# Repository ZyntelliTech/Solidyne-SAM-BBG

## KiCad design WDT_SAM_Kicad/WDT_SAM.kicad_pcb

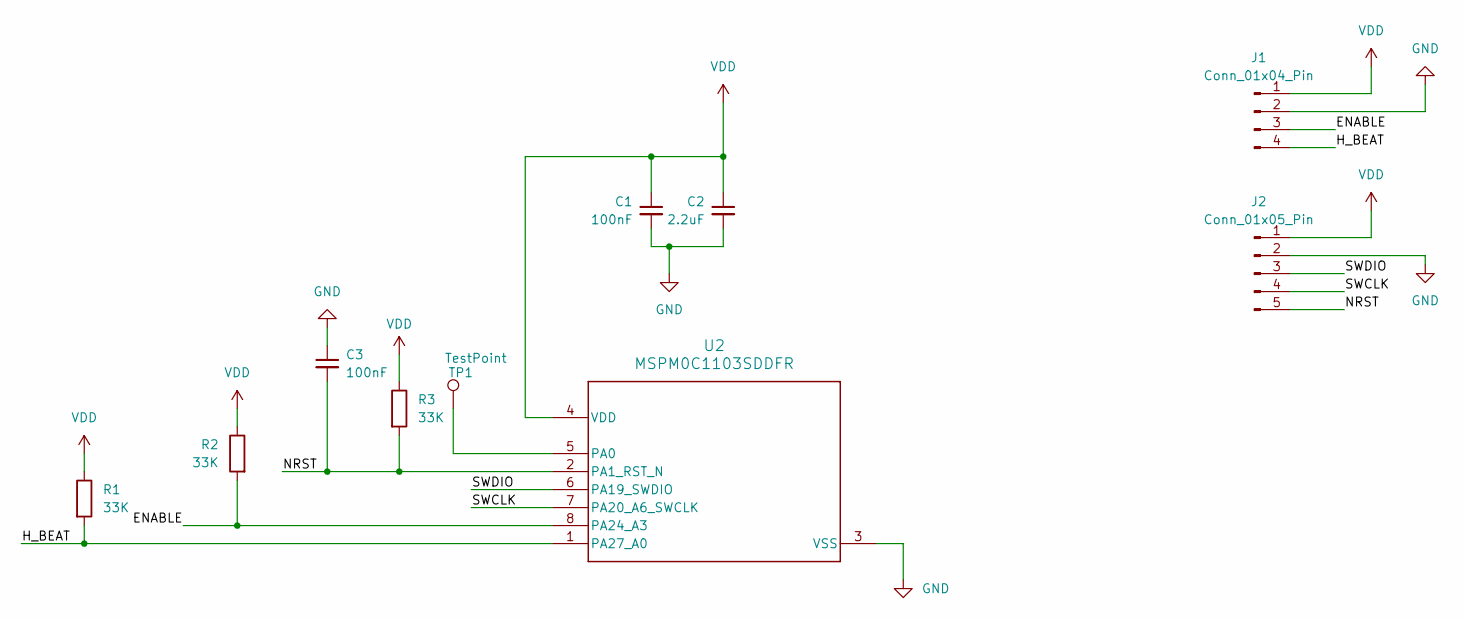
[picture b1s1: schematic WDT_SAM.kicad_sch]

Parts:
C1, C3: 100nF; C_0603_1608Metric_Pad1.08x0.95mm_HandSolder; JLC C1590
C2: 2.2uF; C_0603_1608Metric_Pad1.08x0.95mm_HandSolder; JLC C43922
J1: Conn_01x04_Pin; PinHeader_1x04_P2.54mm_Vertical
J2: Conn_01x05_Pin; PinHeader_1x05_P2.54mm_Vertical_SMD_Pin1Left; JLC C5160788
R1, R2, R3: 33K; R_0603_1608Metric_Pad0.98x0.95mm_HandSolder; JLC C4216
TP1: TestPoint; TestPoint_Pad_1.0x1.0mm
U2: MSPM0C1103SDDFR; DDF0008A-IPC_A; JLC C35962001

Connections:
/ENABLE: J1.3, R2.2, U2.8 (PA24_A3)
/H_BEAT: J1.4, R1.2, U2.1 (PA27_A0)
/NRST: C3.2, J2.5, R3.2, U2.2 (PA1_RST_N)
/SWCLK: J2.4, U2.7 (PA20_A6_SWCLK)
/SWDIO: J2.3, U2.6 (PA19_SWDIO)
GND: C1.2, C2.2, C3.1, J1.2, J2.2, U2.3 (VSS)
unnamed: TP1.1 (1_1), U2.5 (PA0)
VDD: C1.1, C2.1, J1.1, J2.1, R1.1, R2.1, R3.1, U2.4 (VDD)

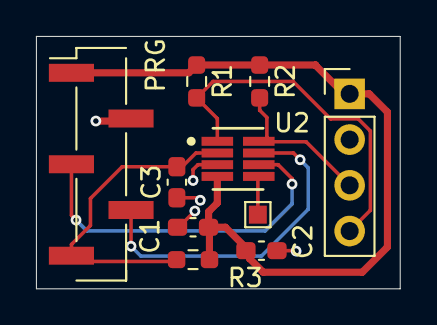
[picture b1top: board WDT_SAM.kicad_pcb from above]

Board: 2 copper layers, 20.2 x 14.0 mm, 10 parts (0 on the bottom side), 8 nets.
